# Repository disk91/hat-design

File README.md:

# hat-design
Raspberry Pi Hat Kicad project

The pourpose of this project is to simplify Raspberry Pi HAT design by providing the source shematics and routing for a HAT compatible shield
This refer to HAT design guide https://github.com/raspberrypi/hats

This GitHub repo is owned by Disk_91, see more detail on hat design in this post from my blog
http://www.disk91.com/?p=1870

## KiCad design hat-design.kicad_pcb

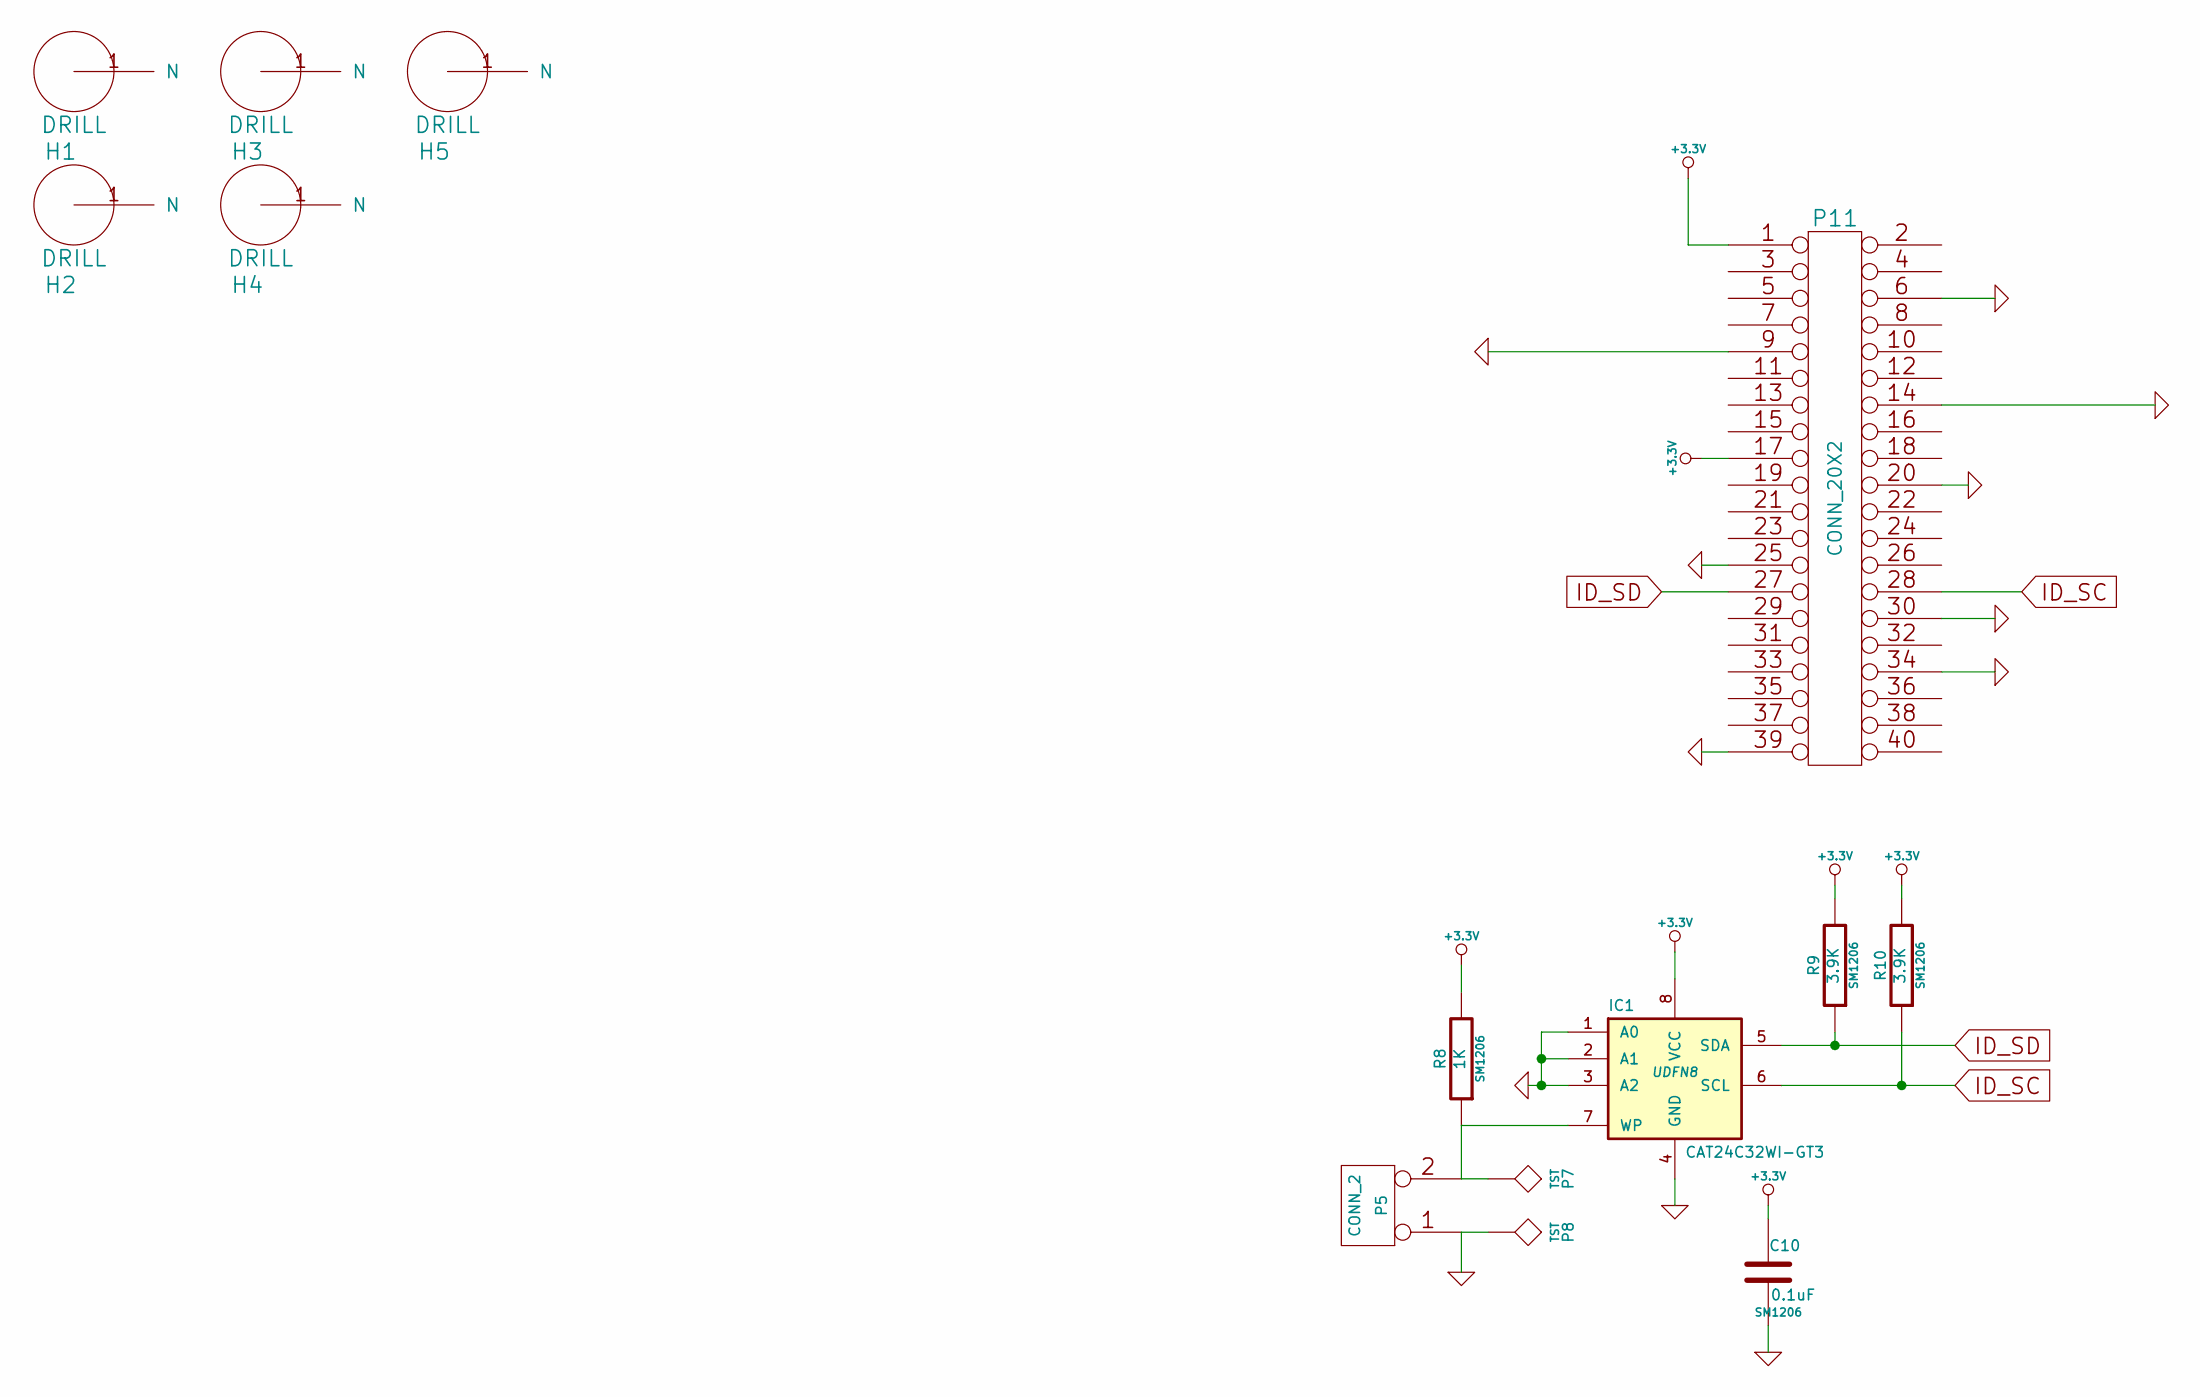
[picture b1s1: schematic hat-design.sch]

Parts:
C10: 0.1uF; SM1206
H1, H2, H3, H4, H5: DRILL
IC1: CAT24C32WI-GT3; UDFN8
P5: CONN_2
P7, P8: TST
P11: CONN_20X2
R8: 1K; SM1206
R9, R10: 3.9K; SM1206

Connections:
+3.3V: C10.1, IC1.8 (VCC), P11.1, P11.17, R8.2, R9.2, R10.2
GND: C10.2, IC1.1 (A0), IC1.2 (A1), IC1.3 (A2), IC1.4 (GND), P5.1, P8.1, P11.6, P11.9, P11.14, P11.20, P11.25, P11.30, P11.34, P11.39
ID_SC: IC1.6 (SCL), P11.28, R10.1
ID_SD: IC1.5 (SDA), P11.27, R9.1
unnamed: IC1.7 (WP), P5.2 (PM), P7.1, R8.1

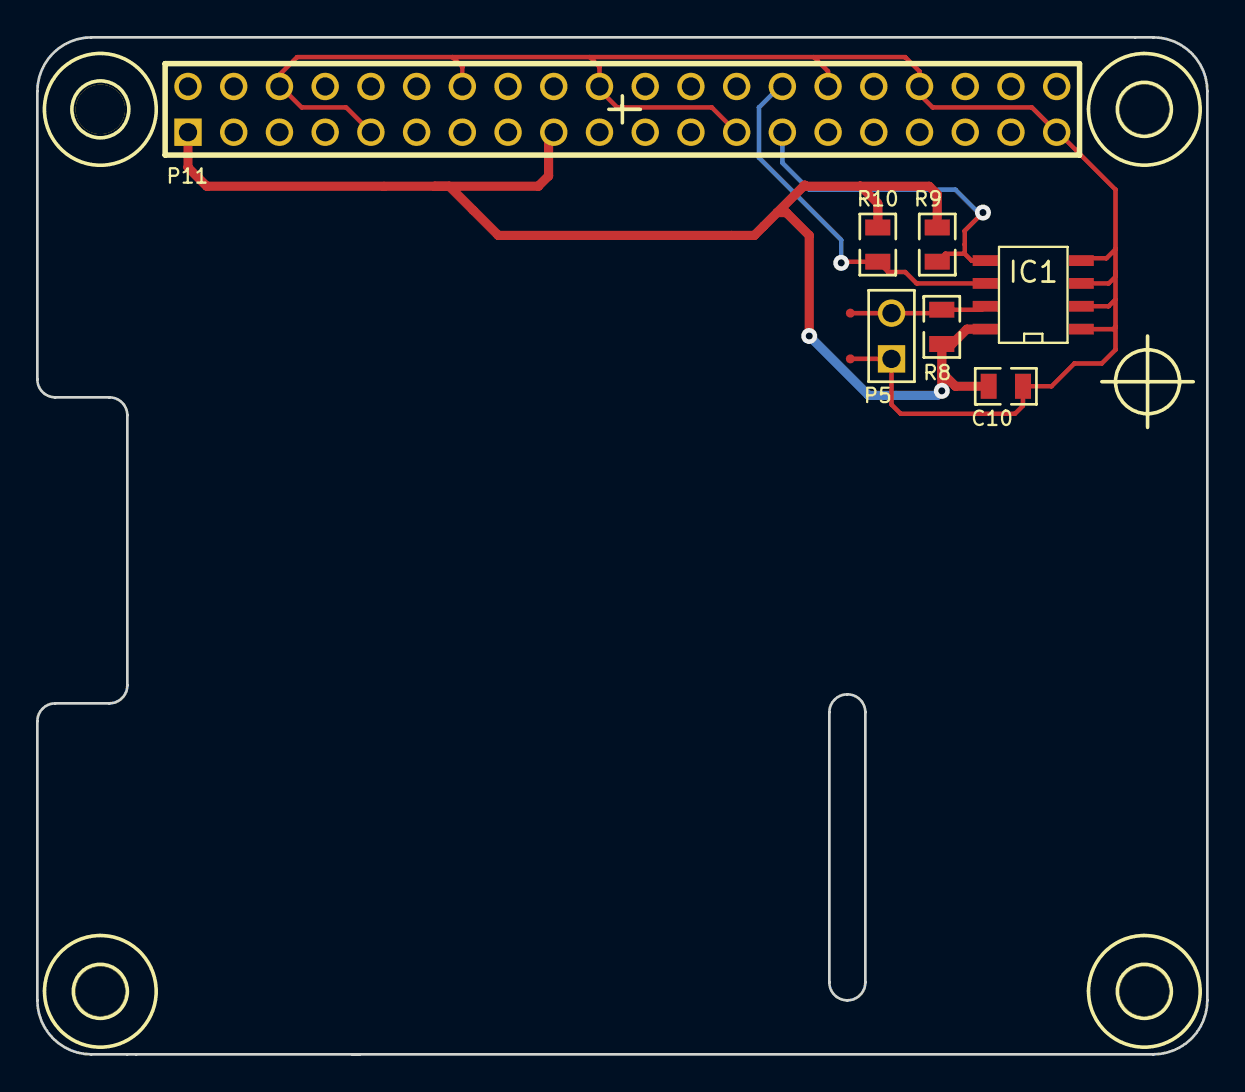
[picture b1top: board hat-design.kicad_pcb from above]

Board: 2 copper layers, 65.0 x 56.5 mm, 14 parts (0 on the bottom side), 5 nets.

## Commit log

2015-03-28 initial version
